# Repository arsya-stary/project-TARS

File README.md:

#TARS PROJECT

ini adalah project individual saya dan team saya untuk membuat robot TARS yang berada di dalam film INTERSTELLAR

gw masih males bikin project nya 3d nya belum dibikin soalnya

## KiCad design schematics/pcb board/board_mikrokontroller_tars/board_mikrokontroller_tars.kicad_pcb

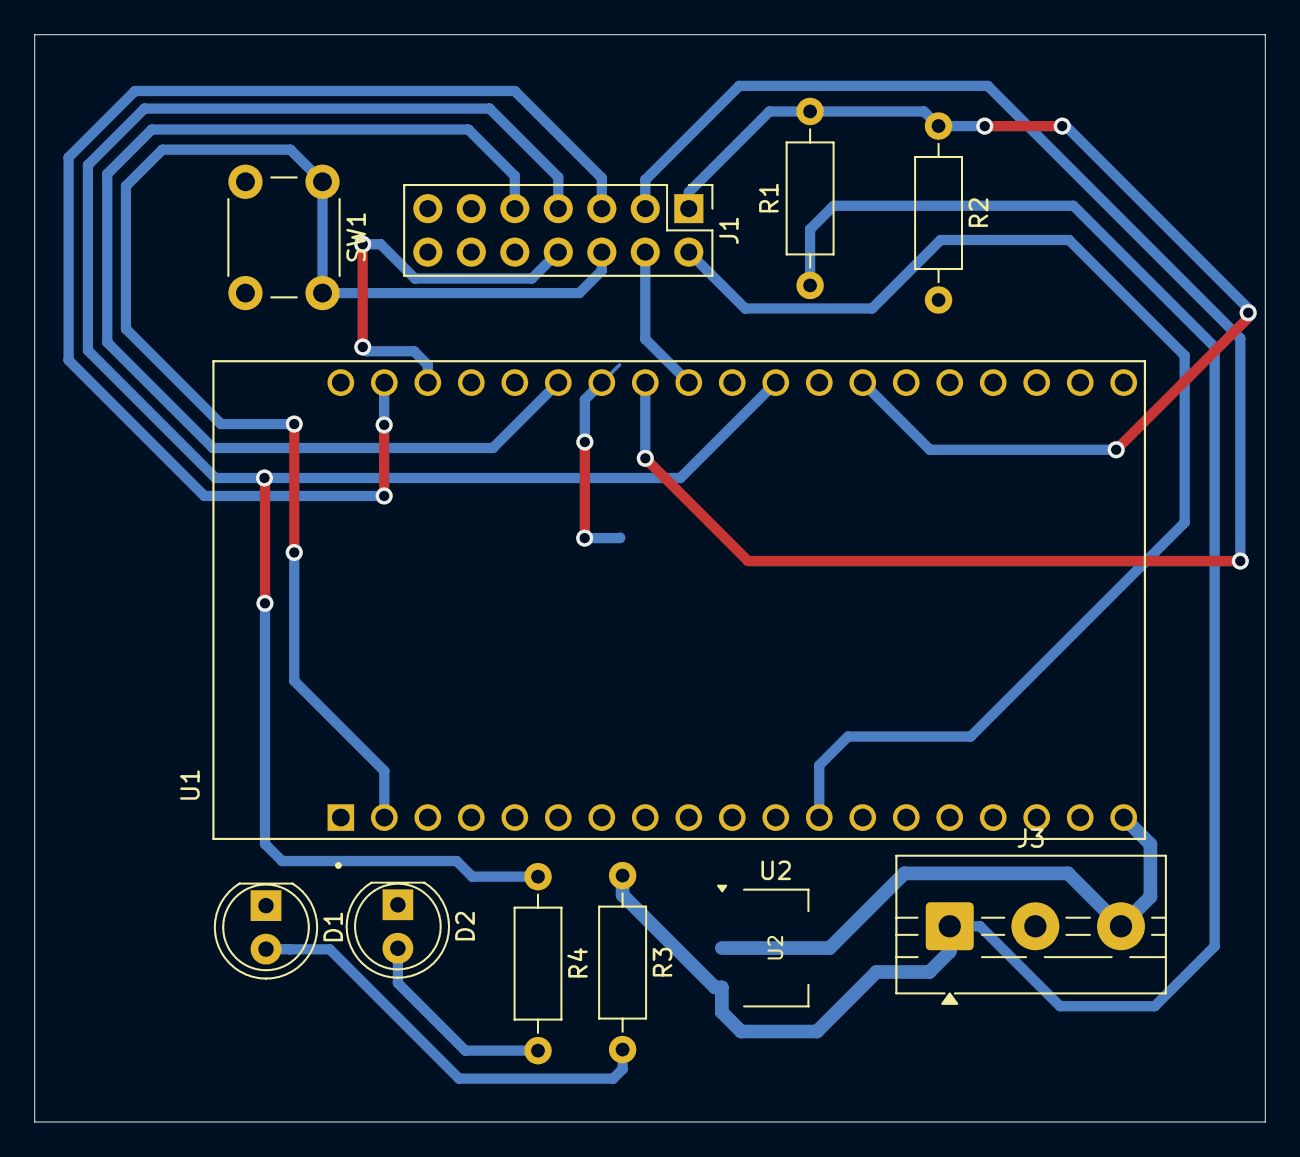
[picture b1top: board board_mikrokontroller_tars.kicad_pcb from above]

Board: 2 copper layers, 71.9 x 63.5 mm, 11 parts (0 on the bottom side), 14 nets.

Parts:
D1: LED; LED_D5.0mm
D2: LED 2; LED_D5.0mm
J1: Conn_02x07_Top_Bottom; PinHeader_2x07_P2.54mm_Vertical
J3: Conn_01x03_Socket; TerminalBlock_MaiXu_MX126-5.0-03P_1x03_P5.00mm
R1, R2: 10k; R_Axial_DIN0207_L6.3mm_D2.5mm_P10.16mm_Horizontal
R3: 1k; R_Axial_DIN0207_L6.3mm_D2.5mm_P10.16mm_Horizontal
R4: 220; R_Axial_DIN0207_L6.3mm_D2.5mm_P10.16mm_Horizontal
SW1: SW_Push; SW_PUSH_6mm
U1: ESP32-DEVKITC-32UE; ESPRESSIF_ESP32-DEVKITC-32UE
U2: AMS1117-5.0; SOT-223-3_TabPin2

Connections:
+5V: J3.3, U1.19 (5V), U2.2 (VO)
Emg_Button: J1.7, R4.1, U1.30 (17)
GND: D1.1 (K), D2.1 (K), J3.2, R2.2, SW1.2, U1.14 (GND), U1.20 (GND), U1.26 (GND), U2.1 (GND)
unnamed: D1.2 (A), R3.2
unnamed: D2.2 (A), R4.2
RST_buttton: J1.6, SW1.1, U1.2 (EN)
SCL (22): J1.8, U1.22
SDA (21): J1.9, U1.25 (21)
Servo_1 left (18): J1.4, U1.28 (18)
Servo_2 right (19): J1.3, U1.27 (19)
Servo_UP-DOWN (23): J1.5, U1.21 (23)
batt+: J3.1, R1.1, R3.1, U2.3 (VI)
level_batery (04): J1.1, R1.2, R2.1, U1.32 (4)
limit_switch (14): J1.2, U1.12 (14)

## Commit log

2025-04-18 include file
    ambass
2025-04-18 Create esp 32
2025-05-13 board tars
    board tars via kicad 9
2025-05-13 new format
2025-05-13 biar ga ilang
2025-05-13 check
2025-05-13 nambahin 3d model
2025-05-18 adding file test serial write
2025-12-02 board update
